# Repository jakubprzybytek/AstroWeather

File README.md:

# AstroWeather

AstroWeather shows whether the coming nights are good for observing the sky. A
serverless API combines astronomy (astronomical dusk and dawn, twilight and moon) with weather
forecasts for a configured location and serves them as a compact text payload.
A Wi-Fi host board fetches that payload every 6 hours and shows six observing
nights on LED displays: its own and up to five chained display boards.

```text
weather supplier ──> sst API (AWS) ──HTTP──> host board ──I2C──> display boards (up to 5)
 (Clearoutside)       GET /astro/{id}       STM32G0B1 +           same PCB, no Wi-Fi
                                            ST67W611M1 Wi-Fi
```

## Repository layout

| Folder | What it holds | Start here |
| --- | --- | --- |
| [`sst/`](sst/) | The server: an [SST](https://sst.dev/) app on AWS (API Gateway, Lambda, DynamoDB, CloudFront), the weather ingestion jobs and a web UI | [architecture](sst/docs/architecture.md) |
| [`firmware/HostControllerA/`](firmware/HostControllerA/) | Firmware for the Wi-Fi host board (STM32G0B1) | [README](firmware/HostControllerA/README.md) |
| [`firmware/DisplayController/`](firmware/DisplayController/) | Firmware for the remote display boards (STM32G070): local display and the I2C link to the host; runs on the first display board | [README](firmware/DisplayController/README.md) |
| [`firmware/Common/`](firmware/Common/) | Code compiled into both firmware images: display encoding and multiplexing, the SCT2xxx driver, the I2C message, task helpers, and their native tests | [README](firmware/Common/README.md) |
| [`firmware/Bypass/`](firmware/Bypass/) | Bench firmware for a separate STM32G0B0 board: a USB-to-UART bridge for talking to and flashing the ST67W611M Wi-Fi module | [README](firmware/Bypass/README.md) |
| [`firmware/Docs/`](firmware/Docs/) | Documentation shared by the firmware projects: development workflow, display, I2C, testing, utilities | [README](firmware/Docs/README.md) |
| [`KiCad/`](KiCad/) | Schematic and PCB of the board. One design is populated as the host or as a display board | [README](KiCad/Docs/README.md) |

## Documentation

**Server (`sst/docs/`)**

- [architecture.md](sst/docs/architecture.md): components, data flow, storage, deployment stages
- [api.md](sst/docs/api.md) and [api-payload.md](sst/docs/api-payload.md): the forecast endpoint and its text payload, which the firmware parses
- [clearoutside-weather-supplier.md](sst/docs/clearoutside-weather-supplier.md): the weather source in use
- [meteosource-weather-supplier.md](sst/docs/meteosource-weather-supplier.md): evaluation of a possible second source
- [development.md](sst/docs/development.md): setup, local development and deployment
- [testing.md](sst/docs/testing.md): unit and integration tests

**Firmware**

Each firmware project starts with a README that lists its features and links
the document for each; documents shared by the projects are in
[firmware/Docs](firmware/Docs/README.md).

- [HostControllerA README](firmware/HostControllerA/README.md): what the host firmware does, its feature status table, quick start and documents
- [DisplayController README](firmware/DisplayController/README.md): the display board firmware, its feature status table, pins and documents
- [Common README](firmware/Common/README.md): the code shared by both firmware images
- [Development.md](firmware/Docs/Development.md): build, flash, debug, connecting over USB, CubeMX rules, for every project
- [Console.md](firmware/HostControllerA/Docs/Console.md): every console command, including Wi-Fi and server settings

**Hardware ([`KiCad/Docs`](KiCad/Docs/README.md))**

- [Hardware_Review.md](KiCad/Docs/Hardware_Review.md): design review, open issues, and measured current draw
- [Display-Issues.md](KiCad/Docs/Display-Issues.md): hardware problems seen on the LED displays, such as the prototype's matrix column faults around `U505`
- [Display_Board_Purchasing.md](KiCad/Docs/Display_Board_Purchasing.md) and [Display_Board_BOM.csv](KiCad/Docs/Display_Board_BOM.csv): parts for the display boards

## Status

- The server is deployed in stages (`prod`, `int`, ...; see
  [architecture.md](sst/docs/architecture.md#web-ui)); the host board fetches
  from the `int` stage.
- The host board fetches, shows and schedules the forecast. The first display
  board runs the DisplayController firmware on the host's I2C bus. See the feature table in the
  [firmware README](firmware/HostControllerA/README.md#features).
- The prototype host board carries hand rework for hardware issues that are not
  yet in the design files. See [Hardware_Review.md](KiCad/Docs/Hardware_Review.md#issues-sorted-by-severity).

## Getting started

- **Server:** [sst/docs/development.md](sst/docs/development.md).
- **Firmware:** the [quick start](firmware/HostControllerA/README.md#quick-start)
  in the firmware README, then [Development.md](firmware/Docs/Development.md)
  to build and flash. The board is pointed at the server with the `api` and
  `wifi` console commands.

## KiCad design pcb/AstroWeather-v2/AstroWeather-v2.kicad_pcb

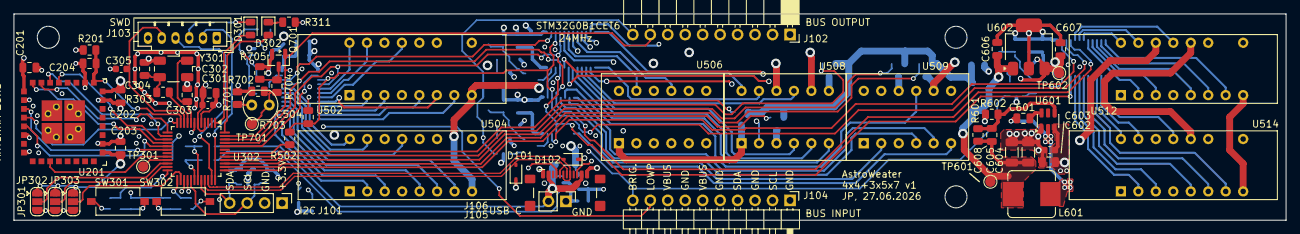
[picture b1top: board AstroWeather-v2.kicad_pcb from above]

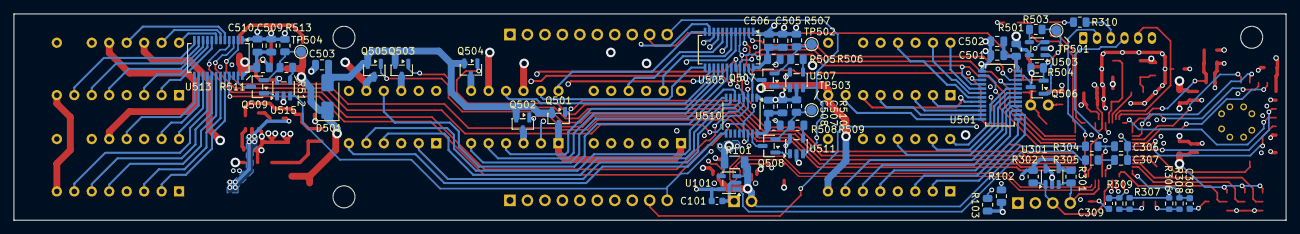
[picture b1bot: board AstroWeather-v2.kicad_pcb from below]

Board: 6 copper layers, 185.0 x 30.0 mm, 127 parts (62 on the bottom side), 140 nets.

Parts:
C101, C301, C305, C308, C309: 100n; C_0603_1608Metric
C201, C202, C203, C503: 10u; C_0805_2012Metric
C204, C601: 100n; C_0805_2012Metric
C302, C502, C505, C507, C509, C606: 4u7; C_0805_2012Metric
C303, C304: 20p; C_0805_2012Metric
C306, C307, C501, C506, C508, C510, C607: 1u; C_0805_2012Metric
C504: 10p; C_0805_2012Metric
C602: 10u/35V; C_0805_2012Metric
C603: 100n/35V; C_0603_1608Metric
C604, C605: 22u; C_1206_3216Metric
C608: 47p; C_0805_2012Metric
D101, D102: D_TVS; D_SOD-323
D301: LED1; D_0805_2012Metric
D302: LED2; D_0805_2012Metric
D501: 1.5V-2V (short); D_SMA
H101, H102, H103: MountingHole; MountingHole_3.2mm_M3
J101: I2C; PinHeader_1x04_P2.54mm_Vertical
J102: Conn_01x10; PinSocket_1x10_P2.54mm_Horizontal
J103: SWD; JST_PH_B6B-PH-K_1x06_P2.00mm_Vertical
J104: Conn_01x10; PinHeader_1x10_P2.54mm_Horizontal
J105: AUX_POWER; PinHeader_1x02_P2.54mm_Vertical
J106: USB; USB_C_Receptacle_GCT_USB4216
JP301: A0; SolderJumper-3_P1.3mm_Open_RoundedPad1.0x1.5mm
JP302: A1; SolderJumper-3_P1.3mm_Open_RoundedPad1.0x1.5mm
JP303: A2; SolderJumper-3_P1.3mm_Open_RoundedPad1.0x1.5mm
L601: SRR6838-33u; L_Bourns_SRP7028A_7.3x6.6mm
Q501, Q502, Q503, Q504, Q505: Si2333DDS; SOT-23
Q506, Q507, Q508, Q509: BC847; SOT-23
Q701: Si2374DS; SOT-23
R101: 0.05; R_1206_3216Metric
R102, R103: 5k1; R_0805_2012Metric
R201: 33k; R_0805_2012Metric
R301, R302: dnp; R_0805_2012Metric
R303: x; R_0805_2012Metric
R304, R305, R601: 100k; R_0805_2012Metric
R306, R307, R308, R309: 10k; R_0603_1608Metric
R310, R311: 2k2; R_0805_2012Metric
R501, R505, R508, R511: 10; R_0805_2012Metric
R502, R503, R506, R509, R512: 1k; R_0805_2012Metric
R504, R507, R510, R513: 4k7 / 10k; R_0805_2012Metric
R602: 19k2; R_0805_2012Metric
R701: 4k7; R_0805_2012Metric
R702: 470k; R_0805_2012Metric
R703: 4k-2M; R_LDR_4.9x4.2mm_P2.54mm_Vertical
R704: 1k5; R_0805_2012Metric
R705: 3k2; R_0805_2012Metric
SW301, SW302: SW_Push; SW_Tactile_SPST_NO_Straight_CK_PTS636Sx25SMTRLFS
TP301, TP501, TP502, TP503, TP504, TP601, TP602, TP701: TestPoint; TestPoint_Pad_D1.5mm
U101: INA180A2; SOT-23-5
U201: ST67W611; ST67W611M1
U301: AT24CS01-STUM; SOT-23-5
U302: STM32G0B1CETx; LQFP-48_7x7mm_P0.5mm
U501: SCT2024CSSG; SSOP-24_3.9x8.7mm_P0.635mm
U502, U504, U512, U514: LFD028BUE-103A
U503, U507, U511, U515: MCP6006T-E/OT; SOT-23-5
U505, U513: SCT2024; SSOP-24_3.9x8.7mm_P0.635mm
U506, U508, U509: LED Matrix 5x7; FYM-7571A
U510: SCT2167; SSOP-16_3.9x4.9mm_P0.635mm
U601: TPS54302; SOT-23-6
U602: MCP1825S; SOT-223-3_TabPin2
Y301: Crystal_GND24_Small; Crystal_SMD_Abracon_ABM3B-4Pin_5.0x3.2mm

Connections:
+3.3V: C101.1, C201.2, C202.1, C203.1, C301.1, C302.1, C607.1, J101.1, J103.1, JP301.1 (A), JP302.1 (A), JP303.1 (A), R201.1, R301.1, R302.1, R306.1, R307.1, R501.1, R505.1, R508.1, R511.1, R701.1, R702.1, TP602.1, U101.5 (V+), U201.9 (VDDIO), U201.16 (VDD33), U201.25 (VDDIO), U301.4 (VCC), U302.4 (VBAT), U302.6 (VDD), U503.5 (V+), U507.5 (V+), U511.5 (V+), U515.5 (V+), U602.3 (VO)
/Display/DIS1_A: U501.7 (Out2), U502.13 (A)
/Display/DIS1_B: U501.6 (Out1), U502.15 (B)
/Display/DIS1_C: U501.9 (Out4), U502.2 (C)
/Display/DIS1_D: U501.8 (Out3), U502.6 (D)
/Display/DIS1_DP: U501.10 (Out5), U502.3 (DP)
/Display/DIS1_E: U501.11 (Out6), U502.5 (E)
/Display/DIS1_F: U501.5 (Out0), U502.16 (F)
/Display/DIS1_G: U501.12 (Out7), U502.7 (G)
/Display/DIS2_A: U501.18 (Out13), U504.13 (A)
/Display/DIS2_B: U501.19 (Out14), U504.15 (B)
/Display/DIS2_C: U501.14 (Out9), U504.2 (C)
/Display/DIS2_D: U501.16 (Out11), U504.6 (D)
/Display/DIS2_DP: U501.13 (Out8), U504.3 (DP)
/Display/DIS2_E: U501.15 (Out10), U504.5 (E)
/Display/DIS2_F: U501.20 (Out15), U504.16 (F)
/Display/DIS2_G: U501.17 (Out12), U504.7 (G)
/Display/DIS3_1: U505.5 (Out0), U506.12 (ROW1)
/Display/DIS3_2: U505.6 (Out1), U506.11 (ROW2)
/Display/DIS3_3: U505.7 (Out2), U506.2 (ROW3)
/Display/DIS3_4: U505.8 (Out3), U506.9 (ROW4)
/Display/DIS3_5: U505.9 (Out4), U506.4 (ROW5)
/Display/DIS3_6: U505.10 (Out5), U506.5 (ROW6)
/Display/DIS3_7: U505.11 (Out6), U506.6 (ROW7)
/Display/DIS3_8: U505.12 (Out7), U508.12 (ROW1)
/Display/DIS3_9: U505.13 (Out8), U508.11 (ROW2)
/Display/DIS3_10: U505.14 (Out9), U508.2 (ROW3)
/Display/DIS3_11: U505.15 (Out10), U508.9 (ROW4)
/Display/DIS3_12: U505.16 (Out11), U508.4 (ROW5)
/Display/DIS3_13: U505.17 (Out12), U508.5 (ROW6)
/Display/DIS3_14: U505.18 (Out13), U508.6 (ROW7)
/Display/DIS3_15: U505.19 (Out14), U509.12 (ROW1)
/Display/DIS3_16: U505.20 (Out15), U509.11 (ROW2)
/Display/DIS3_17: U509.2 (ROW3), U510.5 (Out0)
/Display/DIS3_18: U509.9 (ROW4), U510.6 (Out1)
/Display/DIS3_19: U509.4 (ROW5), U510.7 (Out2)
/Display/DIS3_20: U509.5 (ROW6), U510.8 (Out3)
/Display/DIS3_21: U509.6 (ROW7), U510.9 (Out4)
/Display/DIS4_A: U512.13 (A), U513.5 (Out0)
/Display/DIS4_B: U512.15 (B), U513.6 (Out1)
/Display/DIS4_C: U512.2 (C), U513.8 (Out3)
/Display/DIS4_D: U512.6 (D), U513.11 (Out6)
/Display/DIS4_DP: U512.3 (DP), U513.9 (Out4)
/Display/DIS4_E: U512.5 (E), U513.10 (Out5)
/Display/DIS4_F: U512.16 (F), U513.7 (Out2)
/Display/DIS4_G: U512.7 (G), U513.12 (Out7)
/Display/DIS5_A: U513.13 (Out8), U514.13 (A)
/Display/DIS5_B: U513.14 (Out9), U514.15 (B)
/Display/DIS5_C: U513.20 (Out15), U514.2 (C)
/Display/DIS5_D: U513.17 (Out12), U514.6 (D)
/Display/DIS5_DP: U513.19 (Out14), U514.3 (DP)
/Display/DIS5_E: U513.18 (Out13), U514.5 (E)
/Display/DIS5_F: U513.15 (Out10), U514.16 (F)
/Display/DIS5_G: U513.16 (Out11), U514.7 (G)
/Display/DISPLAY1_EN: Q501.1 (G), U302.41 (PD3)
/Display/DISPLAY2_EN: Q502.1 (G), U302.37 (PA15)
/Display/DISPLAY3_EN: Q503.1 (G), U302.39 (PD1)
/Display/DISPLAY4_EN: Q504.1 (G), U302.40 (PD2)
/Display/DISPLAY5_EN: Q505.1 (G), U302.38 (PD0)
/Display/LED_BRIGHTNESS: J102.10, J104.10, R702.2, R703.2, R704.1, TP701.1, U503.3 (+), U507.3 (+), U511.3 (+), U515.3 (+)
/Display/SCT1_REXT: Q506.3 (C), U501.23 (Rext)
/Display/SCT1_SDO: U501.22 (SDO), U505.2 (SDI)
/Display/SCT1_VDD: C501.1, C502.1, R501.2, U501.24 (VDD)
/Display/SCT2_REXT: Q507.3 (C), U505.23 (Rext)
/Display/SCT2_SDO: U505.22 (SDO), U510.2 (SDI)
/Display/SCT2_VDD: C505.1, C506.1, R505.2, U505.24 (VDD)
/Display/SCT3_REXT: Q508.3 (C), U510.15 (Rext)
/Display/SCT3_SDO: U510.14 (SDO), U513.2 (SDI)
/Display/SCT3_VDD: C507.1, C508.1, R508.2, U510.16 (VDD)
/Display/SCT4_REXT: Q509.3 (C), U513.23 (Rext)
/Display/SCT4_VDD: C509.1, C510.1, R511.2, U513.24 (VDD)
/Display/SCT_CLK: R502.2, U302.42 (SPI3_SCK)
/Display/SCT_CLK_F: C504.1, R502.1, U501.3 (CLK), U505.3 (CLK), U510.3 (CLK), U513.3 (CLK)
/Display/SCT_SDI: U302.44 (SPI3_MOSI), U501.2 (SDI)
/Display/VDD_DIG1: Q501.3 (D), U502.1 (Dig1), U504.1 (Dig1), U506.1 (COL1), U508.1 (COL1), U509.1 (COL1), U512.1 (Dig1), U514.1 (Dig1)
/Display/VDD_DIG2: Q502.3 (D), U502.14 (Dig2), U504.14 (Dig2), U506.3 (COL2), U508.3 (COL2), U509.3 (COL2), U512.14 (Dig2), U514.14 (Dig2)
/Display/VDD_DIG3: Q503.3 (D), U502.11 (Dig3), U504.11 (Dig3), U506.10 (COL3), U508.10 (COL3), U509.10 (COL3), U512.11 (Dig3), U514.11 (Dig3)
/Display/VDD_DIG4: Q504.3 (D), U502.8 (Dig4), U504.8 (Dig4), U506.7 (COL4), U508.7 (COL4), U509.7 (COL4), U512.8 (Dig4), U514.8 (Dig4)
/Display/VDD_DIG5: Q505.3 (D), U502.12 (L), U504.12 (L), U506.8 (COL5), U508.8 (COL5), U509.8 (COL5), U512.12 (L), U514.12 (L)
/Display/VDD_LED: C503.1, D501.2 (A), Q501.2 (S), Q502.2 (S), Q503.2 (S), Q504.2 (S), Q505.2 (S)
/Display/~SCT_EN: U302.46 (PB7), U501.21 (!OE), U505.21 (!OE), U510.13 (!OE), U513.21 (!OE)
/Display/~SCT_LA: U302.45 (PB6), U501.4 (!LA), U505.4 (!LA), U510.4 (!LA), U513.4 (!LA)
/Host Controller/ADDR_0: JP301.2 (C), U302.22 (PB10)
/Host Controller/ADDR_1: JP302.2 (C), U302.23 (PB11)
/Host Controller/ADDR_2: JP303.2 (C), U302.26 (PB14)
/Host Controller/CURRENT_SENSE: R305.2, U101.1
/Host Controller/CURRENT_SENSE_FLTR: C307.1, R305.1, U302.30 (PC6)
/Host Controller/I2C_SCL: J101.3, J102.2, J104.2, R302.2, U301.1 (SCL), U302.29 (I2C1_SCL (PA9))
/Host Controller/I2C_SDA: J101.4, J102.4, J104.4, R301.2, U301.3 (SDA), U302.32 (I2C1_SDA (PA10))
/Host Controller/LED1: D301.2 (A), U302.1 (PC13)
/Host Controller/LED2: D302.2 (A), U302.48 (PB9)
/Host Controller/LOW_POWER_ENABLE: J102.9, J104.9, Q701.1 (G), U302.47 (PB8)
/Host Controller/NRST: C305.1, J103.5, U302.10 (PF2)
/Host Controller/OSC_IN: C303.2, U302.8 (RCC_OSC_IN), Y301.1
/Host Controller/OSC_OUT: R303.1, U302.9 (RCC_OSC_OUT)
/Host Controller/OSC_OUT_PIN: TP301.1, U302.21 (RCC_MCO_2)
/Host Controller/ST67_BOOT: U201.3 (BOOT), U302.20 (PB1)
/Host Controller/ST67_CHIP_EN: C204.2, R201.2, U201.17 (CHIP_EN), U302.11 (PA0)
/Host Controller/ST67_CS: U201.24 (SPI_CS), U302.16 (PA5)
/Host Controller/ST67_MISO: U201.29 (SPI_MISO), U302.17 (SPI1_MISO)
/Host Controller/ST67_MOSI: U201.27 (SPI_MOSI), U302.18 (SPI1_MOSI)
/Host Controller/ST67_RDY: U201.21 (SPI_RDY), U302.15 (PA4)
/Host Controller/ST67_RX: U201.22 (UART_TX), U302.14 (USART2_RX)
/Host Controller/ST67_SCK: U201.28 (SPI_CLK), U302.12 (SPI1_SCK)
/Host Controller/ST67_TX: U201.23 (UART_RX), U302.13 (USART2_TX)
/Host Controller/SWCLK: J103.2, U302.36 (SYS_SWCLK)
/Host Controller/SWDIO: J103.4, U302.35 (SYS_SWDIO)
/Host Controller/SWITCH_1: C309.1, R309.1, U302.25 (PB13)
/Host Controller/SWITCH_2: C308.1, R308.1, U302.24 (PB12)
/Host Controller/UCPD_CC1: J106.A5 (CC1), R103.1, U302.28 (UCPD1_CC1)
/Host Controller/UCPD_CC2: J106.B5 (CC2), R102.1, U302.27 (UCPD1_CC2)
/Host Controller/USB+: D102.2 (A2), J106.A6 (D+), J106.B6 (D+), U302.34 (USB_DP (PA12))
/Host Controller/USB-: D101.2 (A2), J106.A7 (D-), J106.B7 (D-), U302.33 (USB_DM (PA11))
/Host Controller/VOLTAGE_SENS_FLTR: C306.1, R304.1, U302.31 (PC7)
/VBUS_IN: J105.2, J106.A4 (VBUS), J106.A9 (VBUS), J106.B4 (VBUS), J106.B9 (VBUS), R101.1, R304.2, U101.3 (+)
GND: C101.2, C201.1, C202.2, C203.2, C204.1, C301.2, C302.2, C303.1, C304.1, C305.2, C306.2, C307.2, C308.2, C309.2, C501.2, C502.2, C503.2, C504.2, C505.2, C506.2, C507.2, C508.2, C509.2, C510.2, C602.1, C603.2, C604.2, C605.2, C606.2, C607.2, D101.1 (A1), D102.1 (A1), J101.2, J102.1, J102.3, J102.5, J102.7, J103.3, J104.1, J104.3, J104.5, J104.7, J105.1, J106.A1 (GND), J106.A12 (GND), J106.B1 (GND), J106.B12 (GND), JP301.3 (B), JP302.3 (B), JP303.3 (B), Q701.2 (S), R102.2, R103.2, R310.1, R311.1, R504.2, R507.2, R510.2, R513.2, R602.2, R705.1, SW301.1, SW302.1, U101.2 (GND), U201.10 (GND), U201.15 (GND), U201.18 (GND), U201.26 (GND), U201.30 (GND), U201.32 (GND), U301.2 (GND), U301.5 (WP), U302.5 (VREF+), U302.7 (VSS), U501.1 (GND), U503.2 (V-), U505.1 (GND), U507.2 (V-), U510.1 (GND), U511.2 (V-), U513.1 (GND), U515.2 (V-), U601.1 (GND), U602.2 (GND), Y301.2 (G), Y301.4 (G)
unnamed: C304.2, R303.2, Y301.3
unnamed: D301.1 (K), R310.2
unnamed: D302.1 (K), R311.2
unnamed: Q506.1 (B), U503.1
unnamed: Q506.2 (E), R503.1, R504.1, TP501.1
unnamed: Q507.1 (B), U507.1
unnamed: Q507.2 (E), R506.1, R507.1, TP502.1
unnamed: Q508.1 (B), U511.1
unnamed: Q508.2 (E), R509.1, R510.1, TP503.1
unnamed: Q509.1 (B), U515.1
unnamed: Q509.2 (E), R512.1, R513.1, TP504.1
unnamed: Q701.3 (D), R704.2, R705.2
unnamed: R306.2, R308.2, SW301.2
unnamed: R307.2, R309.2, SW302.2
unnamed: R701.2, R703.1
unnamed: R503.2, U503.4 (-)
unnamed: R506.2, U507.4 (-)
unnamed: R509.2, U511.4 (-)
unnamed: R512.2, U515.4 (-)
unnamed: C601.1, U601.6 (BOOT)
unnamed: C608.2, R601.2, R602.1, U601.4 (FB)
unnamed: C601.2, L601.1, U601.2 (SW)
VBUS: C602.2, C603.1, J102.6, J102.8, J104.6, J104.8, R101.2, U101.4 (-), U601.3 (VIN)
VDD: C604.1, C605.1, C606.1, C608.1, D501.1 (K), L601.2, R601.1, TP601.1, U602.1 (VI)

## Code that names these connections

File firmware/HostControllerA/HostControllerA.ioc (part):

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Mcu.Name=STM32G0B1C(B-C-E)Tx
Mcu.Package=LQFP48
Mcu.UserName=STM32G0B1CETx
PA0.GPIOParameters=GPIO_Speed,GPIO_Label
PA0.GPIO_Label=ST67_CHIP_EN
PA0.GPIO_Speed=GPIO_SPEED_FREQ_HIGH
PA0.Signal=GPIO_Output
PA1.GPIOParameters=GPIO_Speed,GPIO_Label
PA1.GPIO_Label=ST67_SCK
PA1.GPIO_Speed=GPIO_SPEED_FREQ_VERY_HIGH
PA1.Mode=Full_Duplex_Master
PA1.Signal=SPI1_SCK
PA10.GPIOParameters=GPIO_Pu
PA10.GPIO_Pu=GPIO_NOPULL
PA10.Mode=I2C
PA10.Signal=I2C1_SDA
PA11\ [PA9].Mode=Device
PA11\ [PA9].Signal=USB_DM
PA12\ [PA10].Mode=Device
PA12\ [PA10].Signal=USB_DP
PA13.Mode=Serial_Wire
PA13.Signal=SYS_SWDIO
PA14-BOOT0.Mode=Serial_Wire
PA14-BOOT0.Signal=SYS_SWCLK
PA15.GPIOParameters=PinState,GPIO_Label
PA15.GPIO_Label=DISPLAY_2_EN
PA15.PinState=GPIO_PIN_SET
PA15.Signal=GPIO_Output
PA2.GPIOParameters=GPIO_Label
PA2.GPIO_Label=ST67_TX
PA2.Mode=Asynchronous
PA2.Signal=USART2_TX
PA3.GPIOParameters=GPIO_Label
PA3.GPIO_Label=ST67_RX
PA3.Mode=Asynchronous
PA3.Signal=USART2_RX
PA4.GPIOParameters=GPIO_PuPd,GPIO_Label,GPIO_ModeDefaultEXTI
PA4.GPIO_Label=ST67_RDY
PA4.GPIO_ModeDefaultEXTI=GPIO_MODE_IT_RISING_FALLING
PA4.GPIO_PuPd=GPIO_PULLDOWN
PA4.Signal=GPXTI4
PA5.GPIOParameters=GPIO_Speed,GPIO_Label
PA5.GPIO_Label=ST67_CS
PA5.GPIO_Speed=GPIO_SPEED_FREQ_HIGH
PA5.Signal=GPIO_Output
PA6.GPIOParameters=GPIO_Speed,GPIO_Label
PA6.GPIO_Label=ST67_MISO
PA6.GPIO_Speed=GPIO_SPEED_FREQ_VERY_HIGH
PA6.Mode=Full_Duplex_Master
PA6.Signal=SPI1_MISO
PA7.GPIOParameters=GPIO_Speed,GPIO_Label
PA7.GPIO_Label=ST67_MOSI
PA7.GPIO_Speed=GPIO_SPEED_FREQ_VERY_HIGH
PA7.Mode=Full_Duplex_Master
PA7.Signal=SPI1_MOSI
PA9.GPIOParameters=GPIO_Pu
PA9.GPIO_Pu=GPIO_NOPULL
PA9.Mode=I2C
PA9.Signal=I2C1_SCL
PB1.GPIOParameters=GPIO_Label
PB1.GPIO_Label=ST67_BOOT
PB1.Signal=GPIO_Output
PB10.GPIOParameters=GPIO_PuPd,GPIO_Label
PB10.GPIO_Label=ADDR_0
PB10.GPIO_PuPd=GPIO_PULLDOWN
PB10.Signal=GPIO_Input
PB11.GPIOParameters=GPIO_PuPd,GPIO_Label
PB11.GPIO_Label=ADDR_1
PB11.GPIO_PuPd=GPIO_PULLDOWN
PB11.Signal=GPIO_Input
PB12.GPIOParameters=GPIO_PuPd,GPIO_Label,GPIO_ModeDefaultEXTI
PB12.GPIO_Label=SWITCH_1
PB12.GPIO_ModeDefaultEXTI=GPIO_MODE_IT_FALLING
PB12.GPIO_PuPd=GPIO_PULLUP
PB12.Signal=GPXTI12
PB13.GPIOParameters=GPIO_PuPd,GPIO_Label,GPIO_ModeDefaultEXTI
PB13.GPIO_Label=SWITCH_2
PB13.GPIO_ModeDefaultEXTI=GPIO_MODE_IT_FALLING
PB13.GPIO_PuPd=GPIO_PULLUP
PB13.Signal=GPXTI13
PB14.GPIOParameters=GPIO_PuPd,GPIO_Label
PB14.GPIO_Label=ADDR_2
PB14.GPIO_PuPd=GPIO_PULLDOWN
PB14.Signal=GPIO_Input
PB2.GPIOParameters=GPIO_Label
PB2.GPIO_Label=CURRENT_SENSE
PB2.Mode=IN10
PB2.Signal=ADC1_IN10
PB3.GPIOParameters=GPIO_Label
PB3.GPIO_Label=SCT_SPI_SCK
PB3.Mode=TX_Only_Simplex_Unidirect_Master
PB3.Signal=SPI3_SCK
PB5.GPIOParameters=GPIO_Label
PB5.GPIO_Label=SCT_SPI_MOSI
PB5.Mode=TX_Only_Simplex_Unidirect_Master
PB5.Signal=SPI3_MOSI
PB6.GPIOParameters=GPIO_Label
PB6.GPIO_Label=SCT_LATCH
PB6.Signal=GPIO_Output
PB7.GPIOParameters=GPIO_Label
PB7.GPIO_Label=SCT_ENABLE
PB7.Signal=GPIO_Output
PB8.GPIOParameters=GPIO_Label
PB8.GPIO_Label=LOW_POWER_EN
PB8.Signal=GPIO_Output
PB9.GPIOParameters=GPIO_Label
PB9.GPIO_Label=LED_2
PB9.Signal=GPIO_Output
PC13.GPIOParameters=GPIO_Label
PC13.GPIO_Label=LED_1
PC13.Signal=GPIO_Output
PC6.Signal=GPIO_Analog
PC7.Signal=GPIO_Analog
PD0.GPIOParameters=PinState,GPIO_Label
PD0.GPIO_Label=DISPLAY_5_EN
PD0.PinState=GPIO_PIN_SET
PD0.Signal=GPIO_Output
PD1.GPIOParameters=PinState,GPIO_Label
PD1.GPIO_Label=DISPLAY_3_EN
PD1.PinState=GPIO_PIN_SET
PD1.Signal=GPIO_Output
PD2.GPIOParameters=PinState,GPIO_Label
PD2.GPIO_Label=DISPLAY_4_EN
PD2.PinState=GPIO_PIN_SET
PD2.Signal=GPIO_Output
PD3.GPIOParameters=PinState,GPIO_Label
PD3.GPIO_Label=DISPLAY_1_EN
PD3.PinState=GPIO_PIN_SET
PD3.Signal=GPIO_Output
PF0-OSC_IN\ (PF0).Mode=HSE-External-Oscillator
PF0-OSC_IN\ (PF0).Signal=RCC_OSC_IN
PF1-OSC_OUT\ (PF1).Mode=HSE-External-Oscillator
PF1-OSC_OUT\ (PF1).Signal=RCC_OSC_OUT
RCC.HSE_VALUE=24000000
RCC.SYSCLKFreq_VALUE=16000000
RCC.SYSCLKSource=RCC_SYSCLKSOURCE_PLLCLK
board=custom

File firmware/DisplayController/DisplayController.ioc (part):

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Mcu.Name=STM32G070CBTx
Mcu.Package=LQFP48
Mcu.UserName=STM32G070CBTx
PA10.Mode=I2C
PA10.Signal=I2C1_SDA
PA13.Mode=Serial_Wire
PA13.Signal=SYS_SWDIO
PA14-BOOT0.Mode=Serial_Wire
PA14-BOOT0.Signal=SYS_SWCLK
PA15.GPIOParameters=PinState,GPIO_Label
PA15.GPIO_Label=DISPLAY_2_EN
PA15.PinState=GPIO_PIN_SET
PA15.Signal=GPIO_Output
PA9.Mode=I2C
PA9.Signal=I2C1_SCL
PB10.GPIOParameters=GPIO_PuPd,GPIO_Label
PB10.GPIO_Label=ADDR_0
PB10.GPIO_PuPd=GPIO_PULLDOWN
PB10.Signal=GPIO_Input
PB11.GPIOParameters=GPIO_PuPd,GPIO_Label
PB11.GPIO_Label=ADDR_1
PB11.GPIO_PuPd=GPIO_PULLDOWN
PB11.Signal=GPIO_Input
PB12.GPIOParameters=GPIO_PuPd,GPIO_Label,GPIO_ModeDefaultEXTI
PB12.GPIO_Label=SWITCH_1
PB12.GPIO_ModeDefaultEXTI=GPIO_MODE_IT_FALLING
PB12.GPIO_PuPd=GPIO_PULLUP
PB12.Signal=GPXTI12
PB13.GPIOParameters=GPIO_PuPd,GPIO_Label,GPIO_ModeDefaultEXTI
PB13.GPIO_Label=SWITCH_2
PB13.GPIO_ModeDefaultEXTI=GPIO_MODE_IT_FALLING
PB13.GPIO_PuPd=GPIO_PULLUP
PB13.Signal=GPXTI13
PB14.GPIOParameters=GPIO_PuPd,GPIO_Label
PB14.GPIO_Label=ADDR_2
PB14.GPIO_PuPd=GPIO_PULLDOWN
PB14.Signal=GPIO_Input
PB3.GPIOParameters=GPIO_Label
PB3.GPIO_Label=SCT_CLK
PB3.Mode=TX_Only_Simplex_Unidirect_Master
PB3.Signal=SPI1_SCK
PB5.GPIOParameters=GPIO_Label
PB5.GPIO_Label=SCT_SDI
PB5.Mode=TX_Only_Simplex_Unidirect_Master
PB5.Signal=SPI1_MOSI
PB6.GPIOParameters=GPIO_Label
PB6.GPIO_Label=SCT_LATCH
PB6.Signal=GPIO_Output
PB7.GPIOParameters=PinState,GPIO_Label
PB7.GPIO_Label=SCT_ENABLE
PB7.PinState=GPIO_PIN_SET
PB7.Signal=GPIO_Output
PB8.GPIOParameters=GPIO_Label
PB8.GPIO_Label=LOW_POWER_ENABLE
PB8.Signal=GPIO_Analog
PB9.GPIOParameters=GPIO_Label
PB9.GPIO_Label=LED_2
PB9.Signal=GPIO_Output
PC13.GPIOParameters=GPIO_Label
PC13.GPIO_Label=LED_1
PC13.Signal=GPIO_Output
PD0.GPIOParameters=PinState,GPIO_Label
PD0.GPIO_Label=DISPLAY_5_EN
PD0.PinState=GPIO_PIN_SET
PD0.Signal=GPIO_Output
PD1.GPIOParameters=PinState,GPIO_Label
PD1.GPIO_Label=DISPLAY_3_EN
PD1.PinState=GPIO_PIN_SET
PD1.Signal=GPIO_Output
PD2.GPIOParameters=PinState,GPIO_Label
PD2.GPIO_Label=DISPLAY_4_EN
PD2.PinState=GPIO_PIN_SET
PD2.Signal=GPIO_Output
PD3.GPIOParameters=PinState,GPIO_Label
PD3.GPIO_Label=DISPLAY_1_EN
PD3.PinState=GPIO_PIN_SET
PD3.Signal=GPIO_Output
RCC.HSE_VALUE=8000000
RCC.SYSCLKFreq_VALUE=16000000
board=custom

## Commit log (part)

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2026-02-12 Init comit
2026-02-13 work
2026-02-21 KiCad work
2026-04-19 Initial plan
2026-04-19 docs: add architecture.md for SST serverless API
    Agent-Logs-Url: https://github.com/jakubprzybytek/AstroWeather/sessions/beafb392-8847-4add-b2ec-366b061f28f0
2026-04-19 docs: define SST architecture and suncalc implementation plan
    Agent-Logs-Url: https://github.com/jakubprzybytek/AstroWeather/sessions/4cb71039-de9e-40a8-a660-44e30d37cec7
2026-04-19 feat(sst): initialize api boilerplate and astro lambda handler
    Agent-Logs-Url: https://github.com/jakubprzybytek/AstroWeather/sessions/9f465143-cd99-4d77-b278-1eb755946901
2026-04-19 refactor(sst): tighten configId type narrowing in astro handler
    Agent-Logs-Url: https://github.com/jakubprzybytek/AstroWeather/sessions/9f465143-cd99-4d77-b278-1eb755946901
2026-04-19 fix(sst): null-safe sun and moon time serialization
    Agent-Logs-Url: https://github.com/jakubprzybytek/AstroWeather/sessions/9f465143-cd99-4d77-b278-1eb755946901
2026-04-19 feat(sst): upgrade sst from v3 to v4.7.9
    Agent-Logs-Url: https://github.com/jakubprzybytek/AstroWeather/sessions/56b96c45-3239-4bc7-8ec0-0287a8571c91
2026-04-19 Add copilot-setup-steps.yml with latest AWS CLI and AWS CDK preinstall
    Agent-Logs-Url: https://github.com/jakubprzybytek/AstroWeather/sessions/7851e216-34f0-43d3-ac1a-b25c9c989a0c
2026-04-19 chore: add devcontainer config with AWS CLI and CDK
    Agent-Logs-Url: https://github.com/jakubprzybytek/AstroWeather/sessions/85027048-b513-42f0-aeef-1bcb7a8c9eec
2026-04-19 chore: remove copilot-setup-steps.yml workflow file
    Agent-Logs-Url: https://github.com/jakubprzybytek/AstroWeather/sessions/9223a4ee-e107-477a-a876-883b336102a1
2026-04-19 feat: add Vitest testing setup and testing.md doc
    Agent-Logs-Url: https://github.com/jakubprzybytek/AstroWeather/sessions/5ceff225-e80e-4b88-9c08-3dc283cda961
2026-04-19 fix: rename integration:live→integration:int script, testin.md→testing.md, add CI section
    Agent-Logs-Url: https://github.com/jakubprzybytek/AstroWeather/sessions/defec800-90a0-4ffa-9620-3e7382ed9895
2026-04-19 refactor: merge integration-int into integration, update testing.md with mocking strategies
    Agent-Logs-Url: https://github.com/jakubprzybytek/AstroWeather/sessions/d11a4f10-308b-4e1d-8b24-4c100790b3d4
2026-04-19 test: add integration tests for GET /astro/{configId}
    Agent-Logs-Url: https://github.com/jakubprzybytek/AstroWeather/sessions/395b554a-eb7e-4700-a2af-cd36dfb1be22
2026-04-20 Integration tests
2026-05-04 some work
2026-06-28 KiCad finishing touches, gerber
